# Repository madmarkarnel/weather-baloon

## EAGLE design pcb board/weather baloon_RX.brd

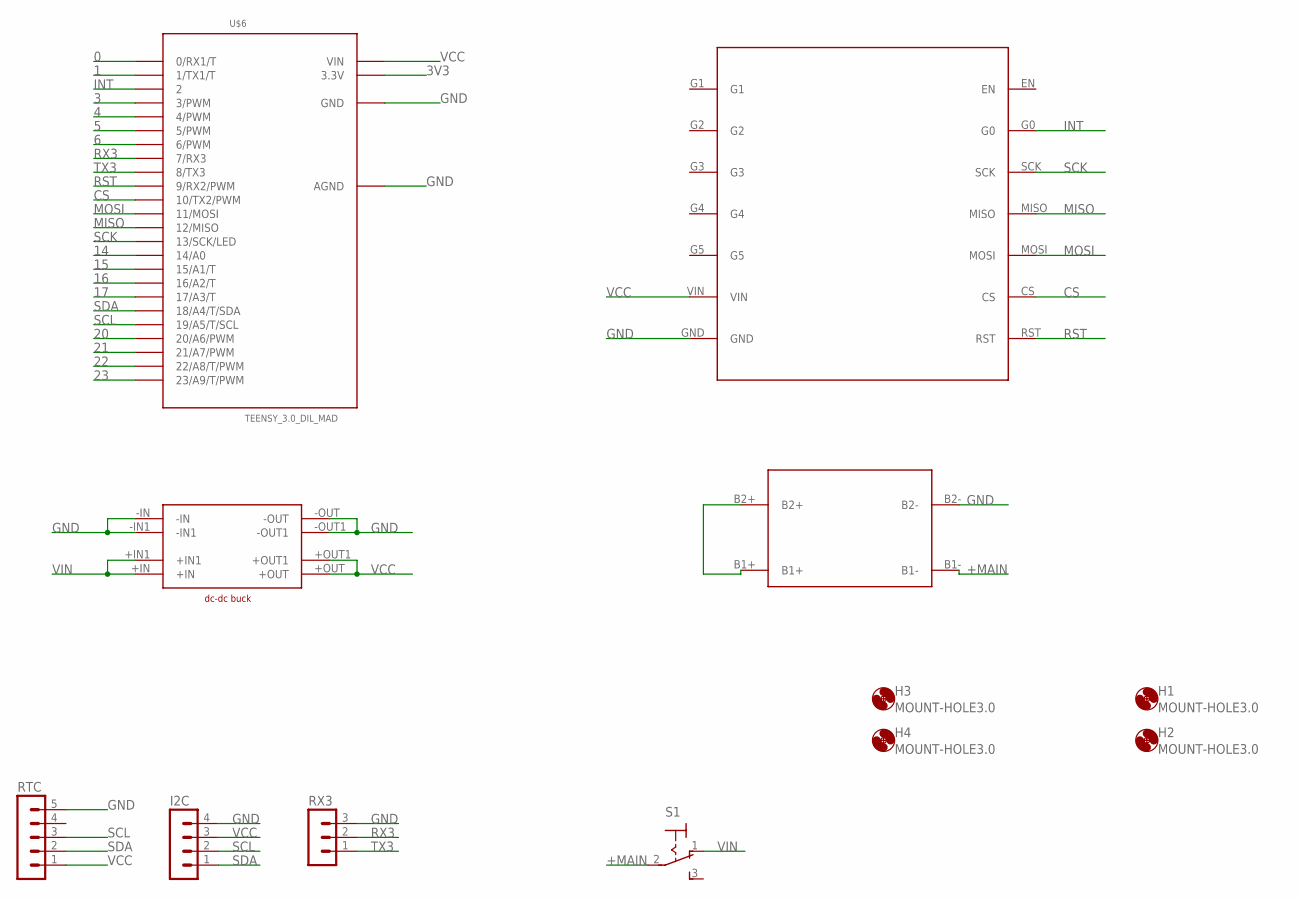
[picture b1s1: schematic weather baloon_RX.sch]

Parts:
H1, H2, H3, H4: MOUNT-HOLE3.0; 3,0
I2C: MA04-1
RTC: MA05-1
RX3: MA03-1
S1: 320-916
U$2: RFM96_MAD; RFM96
U$3: DC-DC_BUCK_MAD; DC-DC_BUCK
U$4: 18650-2
U$6: TEENSY_3.0_DIL_MAD

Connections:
0: U$6.0 (0/RX1/T)
1: U$6.1 (1/TX1/T)
3: U$6.3 (3/PWM)
3V3: U$6.3.3V
4: U$6.4 (4/PWM)
5: U$6.5 (5/PWM)
6: U$6.6 (6/PWM)
14: U$6.14/A0
15: U$6.15/A1 (15/A1/T)
16: U$6.16/A2 (16/A2/T)
17: U$6.17/A3 (17/A3/T)
20: U$6.20/A6 (20/A6/PWM)
21: U$6.21/A7 (21/A7/PWM)
22: U$6.22/A8 (22/A8/T/PWM)
23: U$6.23/A9 (23/A9/T/PWM)
+MAIN: S1.2, U$4.B1-
CS: U$2.CS, U$6.10 (10/TX2/PWM)
GND: I2C.4, RTC.5, RX3.3, U$2.GND, U$3.-IN, U$3.-IN1, U$3.-OUT, U$3.-OUT1, U$4.B2-, U$6.AGND, U$6.GND
INT: U$2.G0, U$6.2
MISO: U$2.MISO, U$6.12 (12/MISO)
MOSI: U$2.MOSI, U$6.11 (11/MOSI)
unnamed: U$4.B1+, U$4.B2+
RST: U$2.RST, U$6.9 (9/RX2/PWM)
RX3: RX3.2, U$6.7 (7/RX3)
SCK: U$2.SCK, U$6.13 (13/SCK/LED)
SCL: I2C.2, RTC.3, U$6.19/A5 (19/A5/T/SCL)
SDA: I2C.1, RTC.2, U$6.18/A4 (18/A4/T/SDA)
TX3: RX3.1, U$6.8 (8/TX3)
VCC: I2C.3, RTC.1, U$2.VIN, U$3.+OUT, U$3.+OUT1, U$6.VIN
VIN: S1.1 (O), U$3.+IN, U$3.+IN1

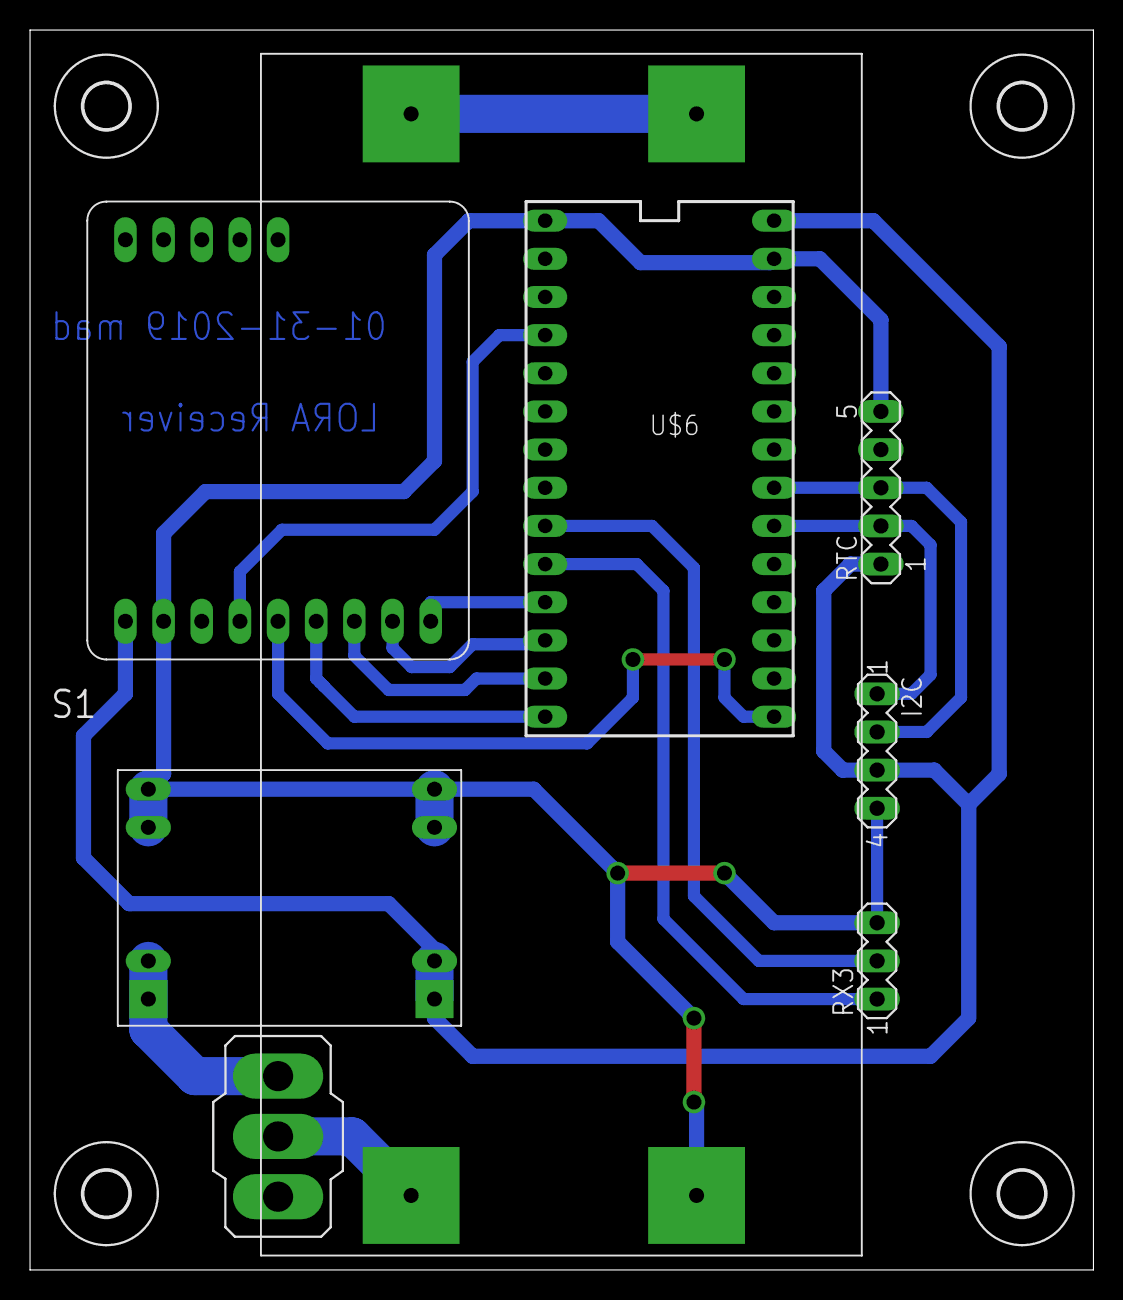
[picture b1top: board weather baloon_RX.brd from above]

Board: 2 copper layers, 70.8 x 82.5 mm, 12 parts (0 on the bottom side), 15 nets.

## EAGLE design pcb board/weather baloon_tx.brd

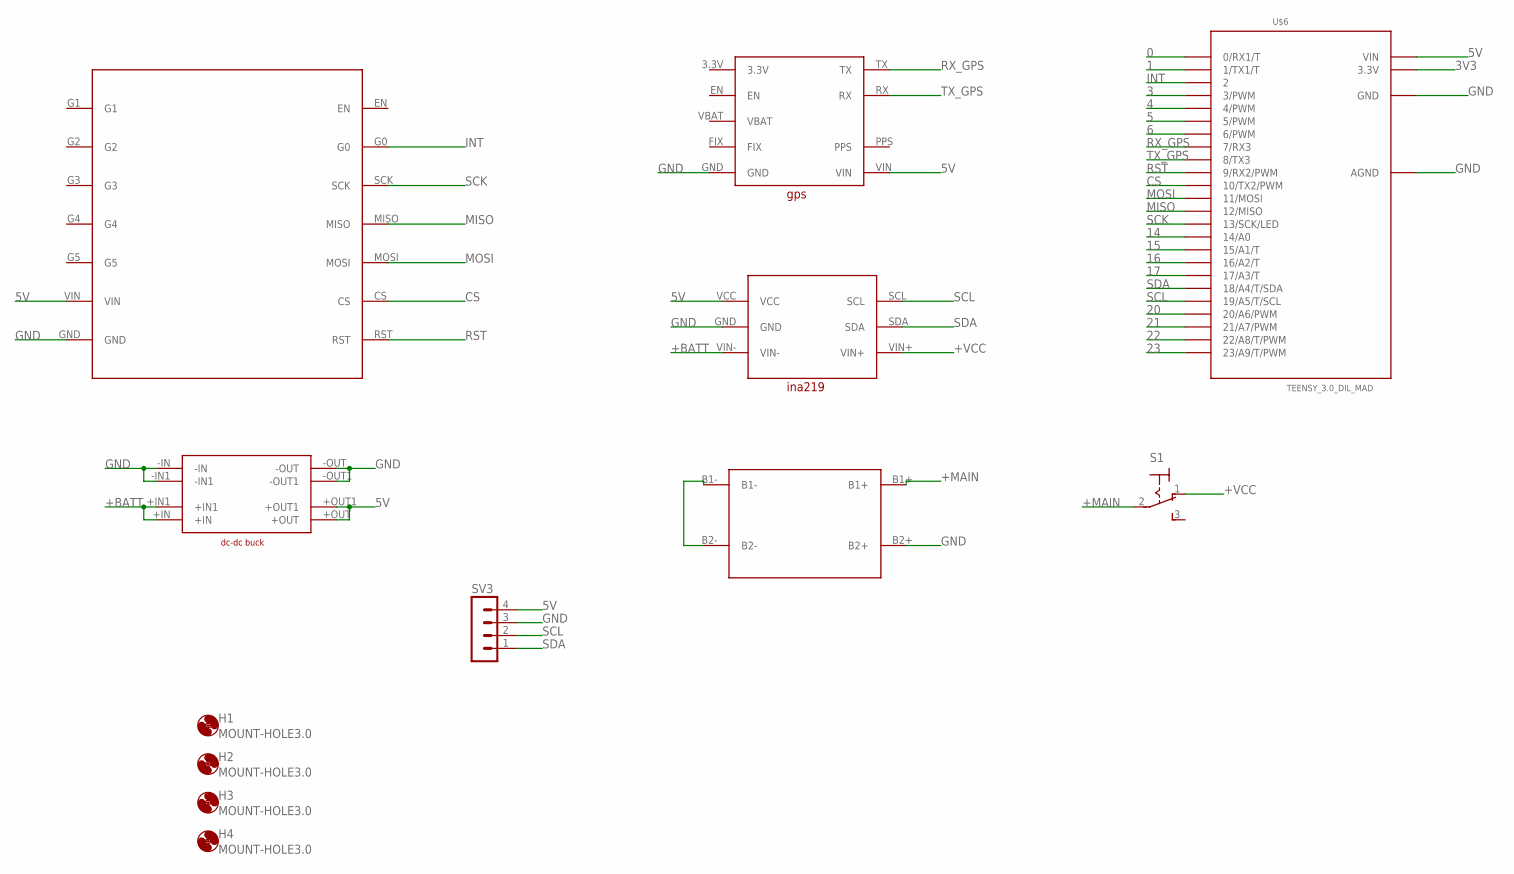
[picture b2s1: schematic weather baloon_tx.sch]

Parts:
H1, H2, H3, H4: MOUNT-HOLE3.0; 3,0
S1: 320-916
SV3: MA04-1
U$1: RFM96_MAD; RFM96
U$2: DC-DC_BUCK_MAD; DC-DC_BUCK
U$3: GPS_MAD; GPS
U$4: 18650-2
U$5: INA219_MAD; INA219
U$6: TEENSY_3.0_DIL_MAD

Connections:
0: U$6.0 (0/RX1/T)
1: U$6.1 (1/TX1/T)
3: U$6.3 (3/PWM)
3V3: U$6.3.3V
4: U$6.4 (4/PWM)
5: U$6.5 (5/PWM)
5V: SV3.4, U$1.VIN, U$2.+OUT, U$2.+OUT1, U$3.VIN, U$5.VCC, U$6.VIN
6: U$6.6 (6/PWM)
14: U$6.14/A0
15: U$6.15/A1 (15/A1/T)
16: U$6.16/A2 (16/A2/T)
17: U$6.17/A3 (17/A3/T)
20: U$6.20/A6 (20/A6/PWM)
21: U$6.21/A7 (21/A7/PWM)
22: U$6.22/A8 (22/A8/T/PWM)
23: U$6.23/A9 (23/A9/T/PWM)
+BATT: U$2.+IN, U$2.+IN1, U$5.VIN-
+MAIN: S1.2, U$4.B1+
+VCC: S1.1 (O), U$5.VIN+
CS: U$1.CS, U$6.10 (10/TX2/PWM)
GND: SV3.3, U$1.GND, U$2.-IN, U$2.-IN1, U$2.-OUT, U$2.-OUT1, U$3.GND, U$4.B2+, U$5.GND, U$6.AGND, U$6.GND
INT: U$1.G0, U$6.2
MISO: U$1.MISO, U$6.12 (12/MISO)
MOSI: U$1.MOSI, U$6.11 (11/MOSI)
unnamed: U$4.B1-, U$4.B2-
RST: U$1.RST, U$6.9 (9/RX2/PWM)
RX_GPS: U$3.TX, U$6.7 (7/RX3)
SCK: U$1.SCK, U$6.13 (13/SCK/LED)
SCL: SV3.2, U$5.SCL, U$6.19/A5 (19/A5/T/SCL)
SDA: SV3.1, U$5.SDA, U$6.18/A4 (18/A4/T/SDA)
TX_GPS: U$3.RX, U$6.8 (8/TX3)

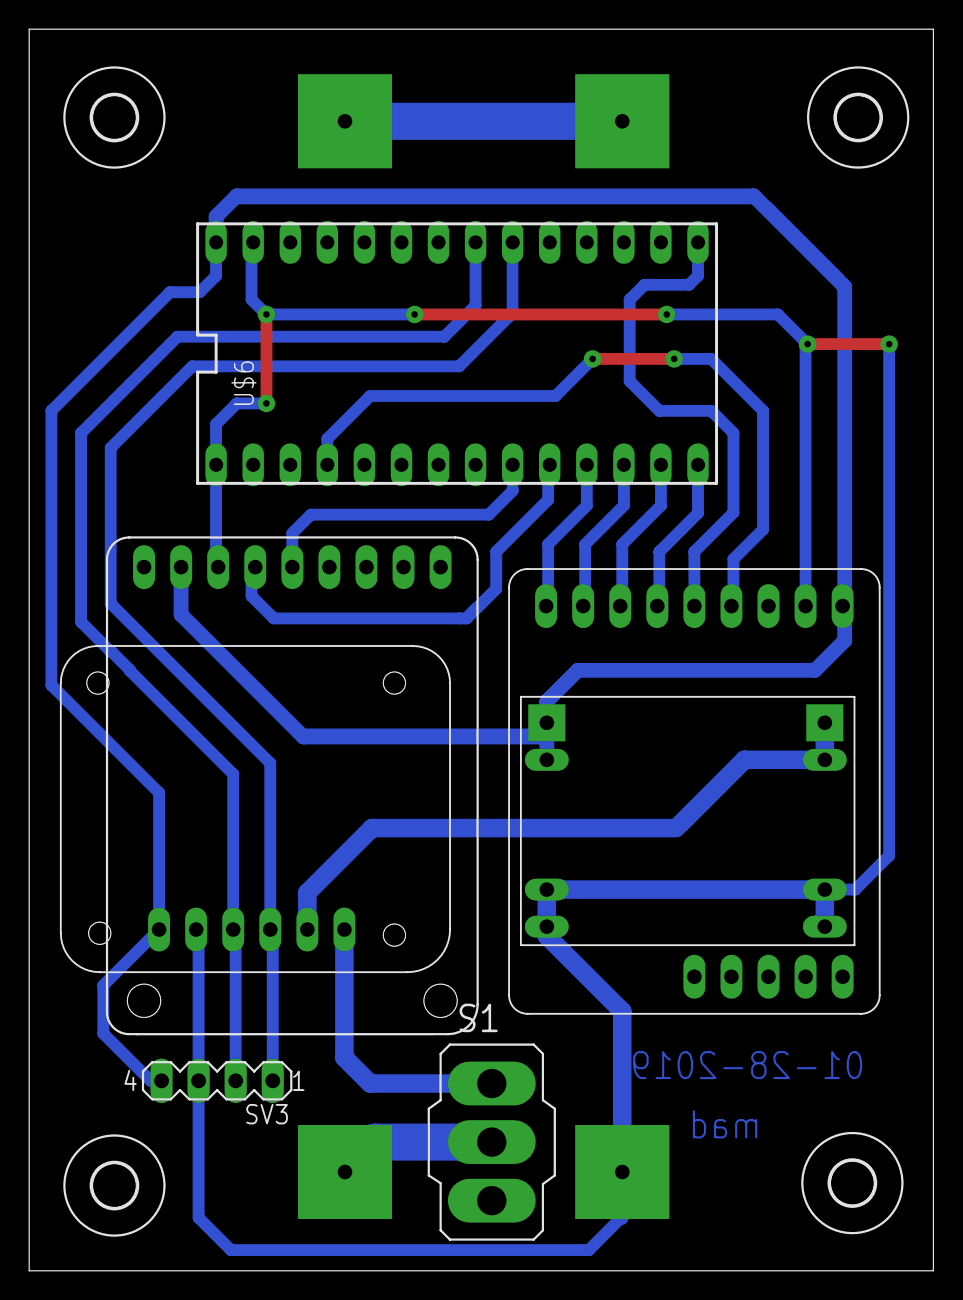
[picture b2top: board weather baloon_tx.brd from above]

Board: 2 copper layers, 62.0 x 85.1 mm, 12 parts (1 on the bottom side), 16 nets.

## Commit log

2019-02-05 final working
2019-02-05 pcb board file
2019-02-05 setting time receiver time
2019-02-05 updated constants i.e. pressure, temperature, humidity
2019-02-05 updated frame of schematic
2019-02-05 updated present constants
